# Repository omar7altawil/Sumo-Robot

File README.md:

# Sumo-Robot

Our project is about designing, assembling and programming our own Sumo
Robot. We had a budget of 100 US Dollar and were not allowed to exceed
it.At the end of the semester, there were a competition to see which Sumo
Robot is better and we will hopefully win the competition.

for the full report read(Project_micro.pdf)

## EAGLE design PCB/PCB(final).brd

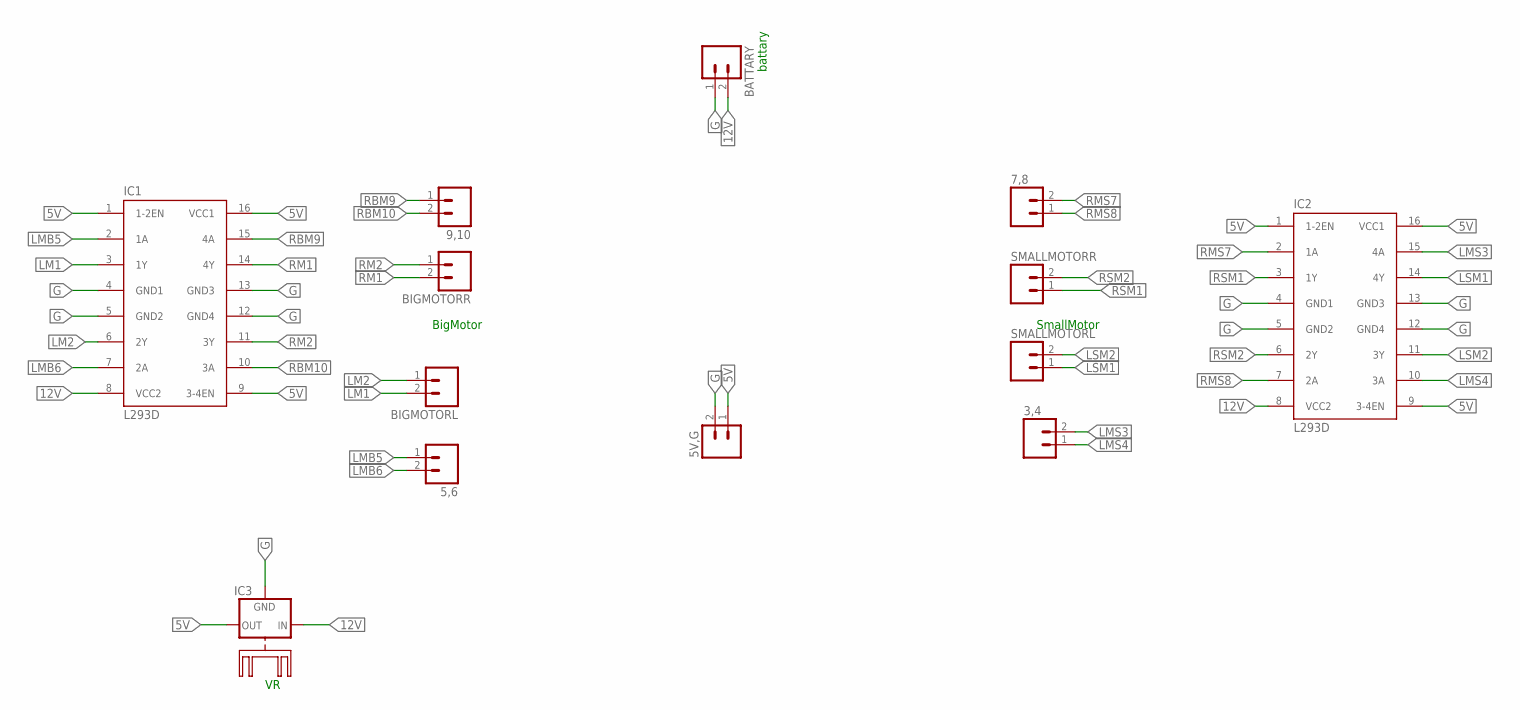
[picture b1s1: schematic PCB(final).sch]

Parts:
3,4, 5,6, 5V,G, 7,8, 9,10: M02; 02P
BATTARY: M02; 02P
BIGMOTORL: M02; 02P
BIGMOTORR: M02; 02P
IC1, IC2: L293D; DIL16
IC3: 78XXH
SMALLMOTORL: M02; 02P
SMALLMOTORR: M02; 02P

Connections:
5V: 5V,G.1, IC1.1 (1-2EN), IC1.9 (3-4EN), IC1.16 (VCC1), IC2.1 (1-2EN), IC2.9 (3-4EN), IC2.16 (VCC1), IC3.OUT
12V: BATTARY.2, IC1.8 (VCC2), IC2.8 (VCC2), IC3.IN
G: 5V,G.2, BATTARY.1, IC1.4 (GND1), IC1.5 (GND2), IC1.12 (GND4), IC1.13 (GND3), IC2.4 (GND1), IC2.5 (GND2), IC2.12 (GND4), IC2.13 (GND3), IC3.GND
LM1: BIGMOTORL.2, IC1.3 (1Y)
LM2: BIGMOTORL.1, IC1.6 (2Y)
LMB5: 5,6.1, IC1.2 (1A)
LMB6: 5,6.2, IC1.7 (2A)
LMS3: 3,4.2, IC2.15 (4A)
LMS4: 3,4.1, IC2.10 (3A)
LSM1: IC2.14 (4Y), SMALLMOTORL.1
LSM2: IC2.11 (3Y), SMALLMOTORL.2
RBM9: 9,10.1, IC1.15 (4A)
RBM10: 9,10.2, IC1.10 (3A)
RM1: BIGMOTORR.2, IC1.14 (4Y)
RM2: BIGMOTORR.1, IC1.11 (3Y)
RMS7: 7,8.2, IC2.2 (1A)
RMS8: 7,8.1, IC2.7 (2A)
RSM1: IC2.3 (1Y), SMALLMOTORR.1
RSM2: IC2.6 (2Y), SMALLMOTORR.2

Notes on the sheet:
battary
BigMotor
SmallMotor

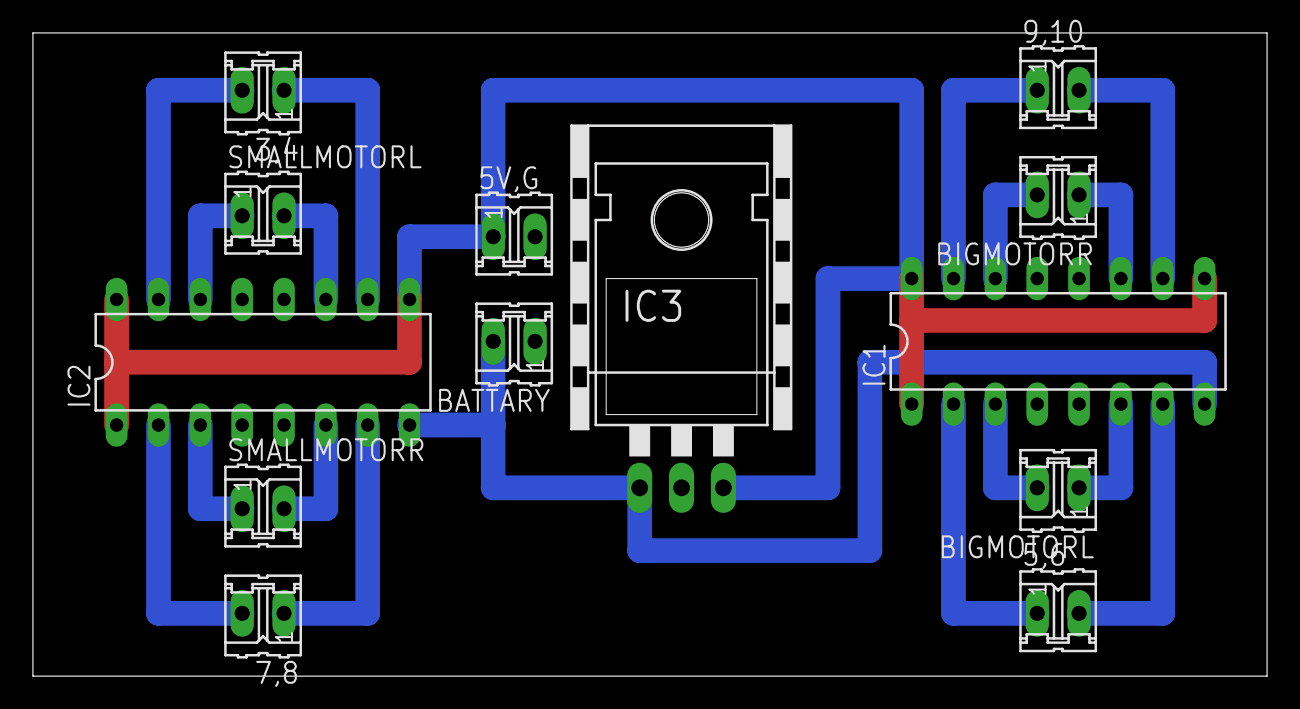
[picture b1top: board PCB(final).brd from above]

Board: 2 copper layers, 74.9 x 39.0 mm, 13 parts (0 on the bottom side), 19 nets.

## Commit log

2019-02-12 final
